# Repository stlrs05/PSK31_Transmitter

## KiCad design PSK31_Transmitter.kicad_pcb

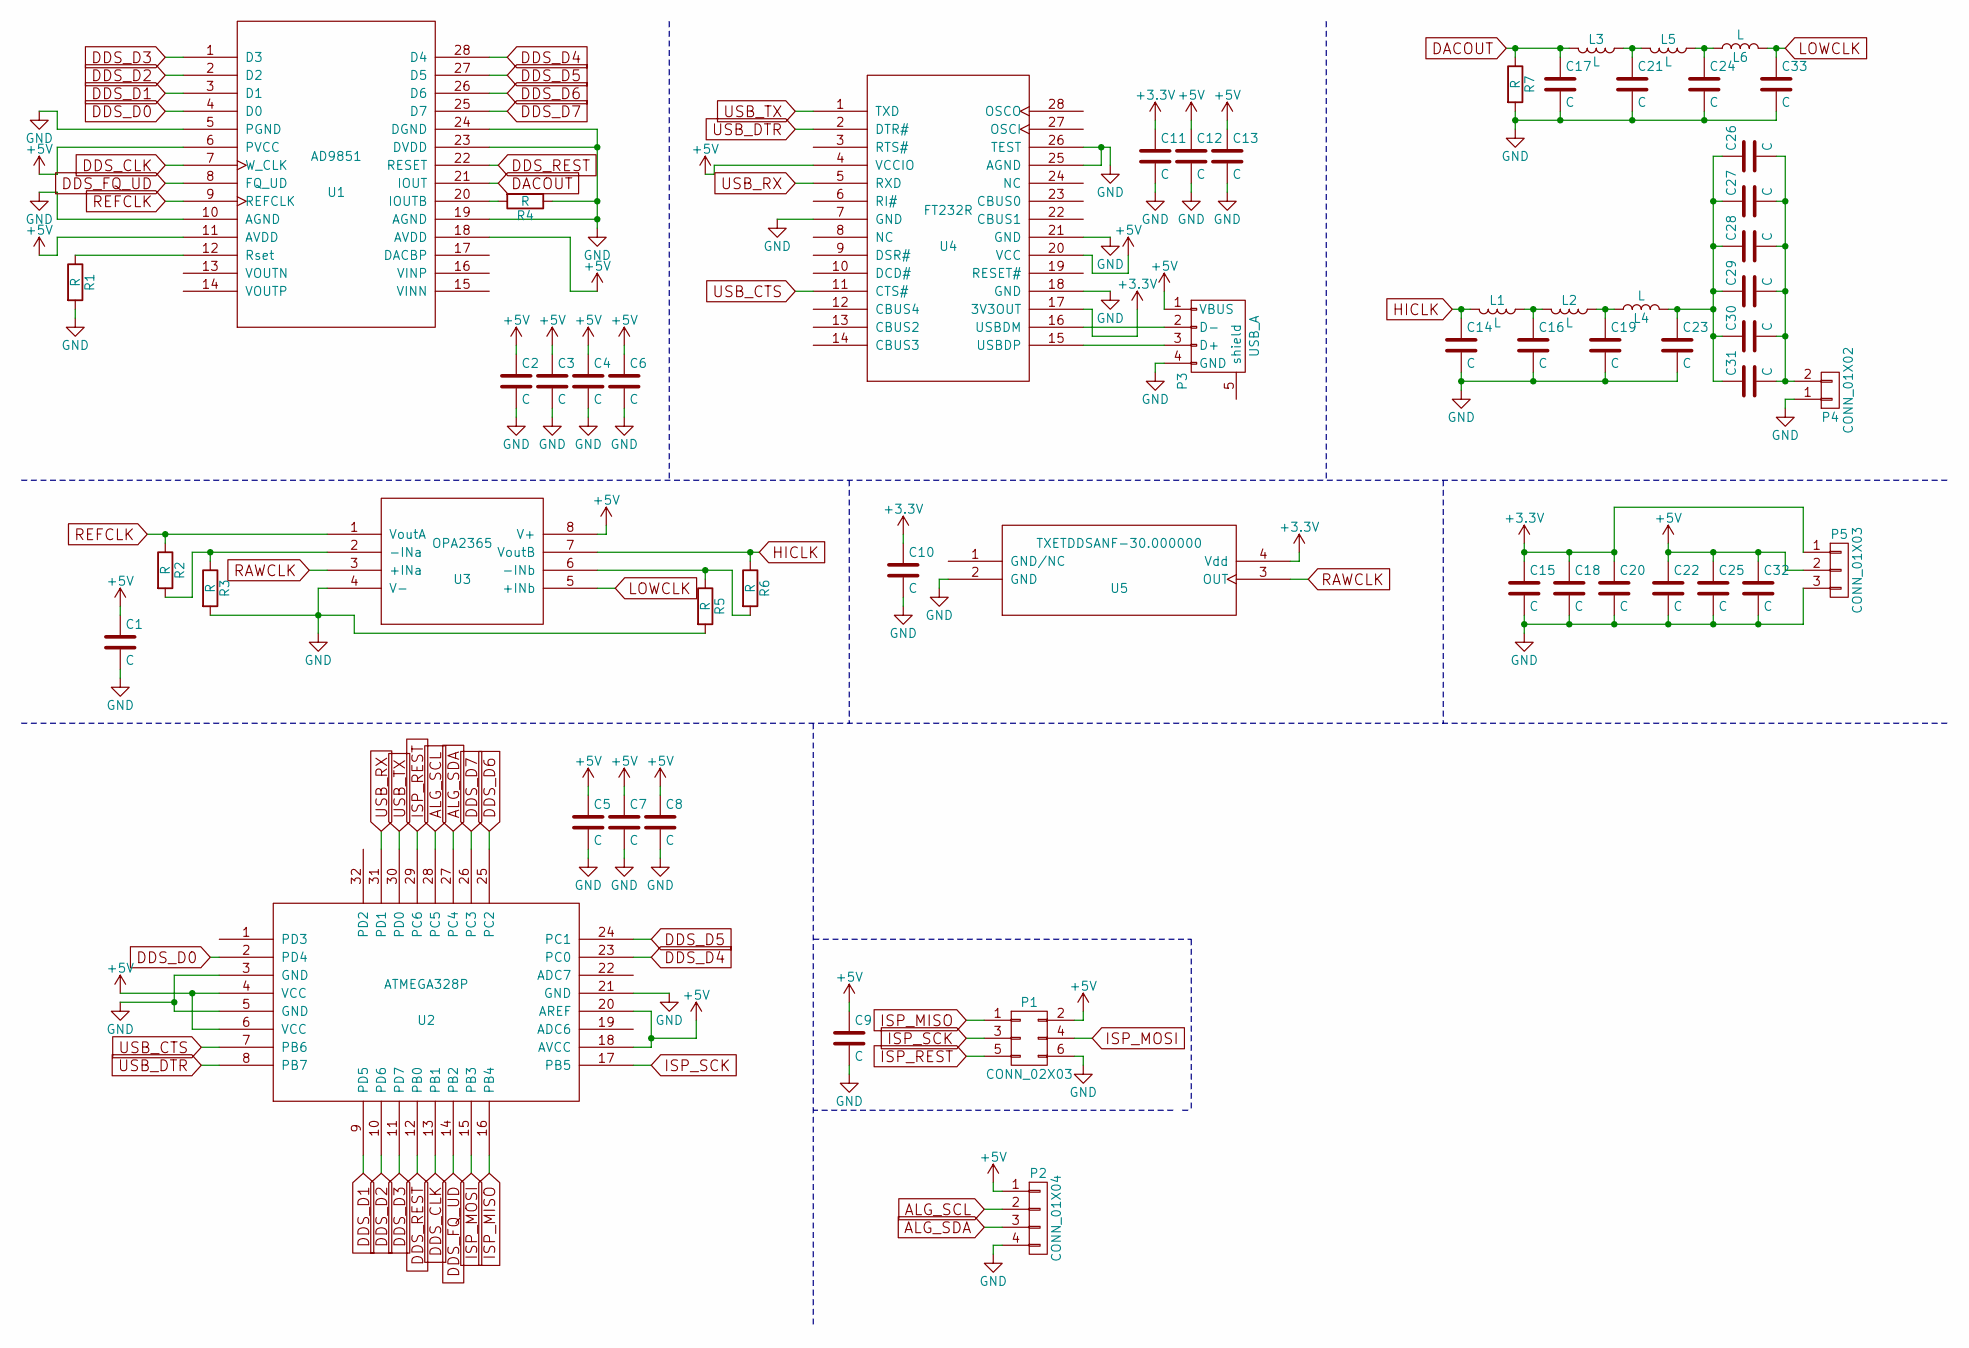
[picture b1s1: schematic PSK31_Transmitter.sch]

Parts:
C1, C2, C3, C4, C5, C6, C7, C8, C9, C10, C11, C12, C13, C14, C15, C16, C17, C18, C19, C20, C21, C22, C23, C24, C25, C26, C27, C28, C29, C30, C31, C32, C33: C; C_1206_HandSoldering
L1, L2, L3, L4, L5, L6: L; L_1206_Handsoldering
P1: CONN_02X03; Pin_Header_Angled_2x03_Pitch2.54mm
P2: CONN_01X04; Pin_Header_Angled_1x04_Pitch2.54mm
P3: USB_A
P4: CONN_01X02; UMC
P5: CONN_01X03; Pin_Header_Angled_1x03_Pitch2.54mm
R1, R2, R3, R4, R5, R6, R7: R; R_1206_HandSoldering
U1: AD9851; SSOP-28_5.3x10.2mm_Pitch0.65mm
U2: ATMEGA328P; TQFP-32_7x7mm_Pitch0.8mm
U3: OPA2365; SOIC-8_3.9x4.9mm_Pitch1.27mm
U4: FT232R; SSOP-28_5.3x10.2mm_Pitch0.65mm
U5: TXETDDSANF-30.000000; Oscillator_SMD_TXC_7C-4pin_5.0x3.2mm_HandSoldering

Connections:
+3V3: C10.1, C11.1, C15.1, C18.1, C20.1, P5.1, U4.17 (3V3OUT), U5.4 (Vdd)
+5V: C1.1, C2.1, C3.1, C4.1, C5.1, C6.1, C7.1, C8.1, C9.1, C12.1, C13.1, C22.1, C25.1, C32.1, P1.2, P2.1, P3.1 (VBUS), P5.2, U1.6 (PVCC), U1.11 (AVDD), U1.18 (AVDD), U2.4 (VCC), U2.6 (VCC), U2.18 (AVCC), U2.20 (AREF), U3.8 (V+), U4.4 (VCCIO), U4.20 (VCC)
ALG_SCL: P2.2, U2.28 (PC5)
ALG_SDA: P2.3, U2.27 (PC4)
DACOUT: C17.1, L3.2, R7.1, U1.21 (IOUT)
DDS_CLK: U1.7 (W_CLK), U2.13 (PB1)
DDS_D0: U1.4 (D0), U2.2 (PD4)
DDS_D1: U1.3 (D1), U2.9 (PD5)
DDS_D2: U1.2 (D2), U2.10 (PD6)
DDS_D3: U1.1 (D3), U2.11 (PD7)
DDS_D4: U1.28 (D4), U2.23 (PC0)
DDS_D5: U1.27 (D5), U2.24 (PC1)
DDS_D6: U1.26 (D6), U2.25 (PC2)
DDS_D7: U1.25 (D7), U2.26 (PC3)
DDS_FQ_UD: U1.8 (FQ_UD), U2.14 (PB2)
DDS_REST: U1.22 (RESET), U2.12 (PB0)
GND: C1.2, C2.2, C3.2, C4.2, C5.2, C6.2, C7.2, C8.2, C9.2, C10.2, C11.2, C12.2, C13.2, C14.2, C15.2, C16.2, C17.2, C18.2, C19.2, C20.2, C21.2, C22.2, C23.2, C24.2, C25.2, C32.2, C33.2, P1.6, P2.4, P3.4 (GND), P4.1, P5.3, R1.2, R3.2, R4.1, R5.2, R7.2, U1.5 (PGND), U1.10 (AGND), U1.19 (AGND), U1.23 (DVDD), U1.24 (DGND), U2.3 (GND), U2.5 (GND), U2.21 (GND), U3.4 (V-), U4.7 (GND), U4.18 (GND), U4.21 (GND), U4.25 (AGND), U4.26 (TEST), U5.2 (GND)
HICLK: C14.1, L1.2, R6.1, U3.7 (VoutB)
ISP_MISO: P1.1, U2.16 (PB4)
ISP_MOSI: P1.4, U2.15 (PB3)
ISP_REST: P1.5, U2.29 (PC6)
ISP_SCK: P1.3, U2.17 (PB5)
LOWCLK: C33.1, L6.2, U3.5 (+INb)
unnamed: C16.1, L1.1, L2.2
unnamed: C19.1, L2.1, L4.1
unnamed: C21.1, L3.1, L5.2
unnamed: C23.1, C26.1, C27.1, C28.1, C29.1, C30.1, C31.1, L4.2
unnamed: C24.1, L5.1, L6.1
unnamed: C26.2, C27.2, C28.2, C29.2, C30.2, C31.2, P4.2
unnamed: P3.2 (D-), U4.16 (USBDM)
unnamed: P3.3 (D+), U4.15 (USBDP)
unnamed: R1.1, U1.12 (Rset)
unnamed: R2.2, R3.1, U3.2 (-INa)
unnamed: R4.2, U1.20 (IOUTB)
unnamed: R5.1, R6.2, U3.6 (-INb)
RAWCLK: U3.3 (+INa), U5.3 (OUT)
REFCLK: R2.1, U1.9 (REFCLK), U3.1 (VoutA)
USB_CTS: U2.7 (PB6), U4.11 (CTS#)
USB_DTR: U2.8 (PB7), U4.2 (DTR#)
USB_RX: U2.31 (PD1), U4.5 (RXD)
USB_TX: U2.30 (PD0), U4.1 (TXD)

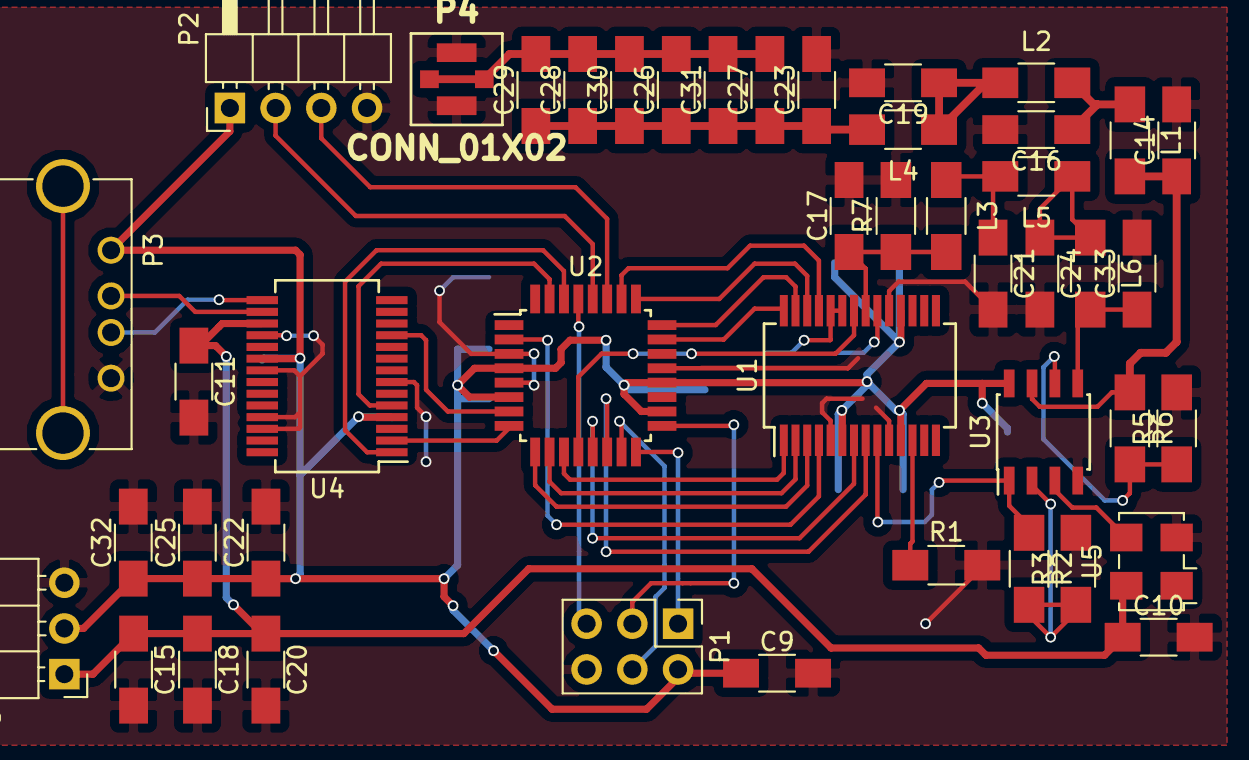
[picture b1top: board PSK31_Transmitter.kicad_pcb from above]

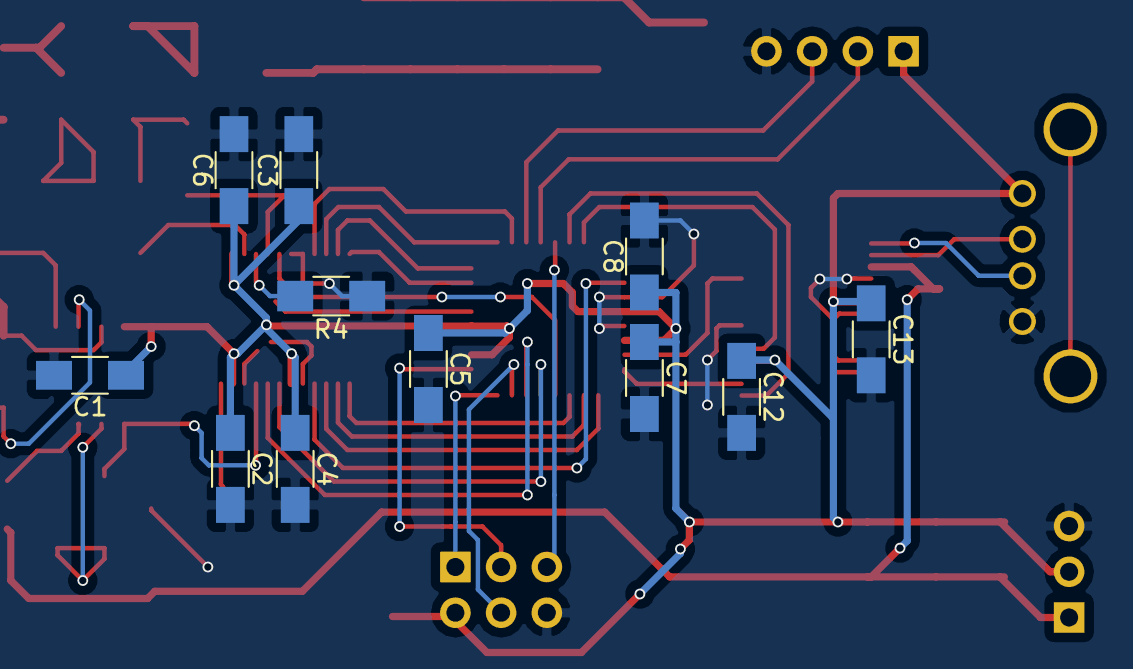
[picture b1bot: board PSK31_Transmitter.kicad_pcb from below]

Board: 2 copper layers, 56 parts (11 on the bottom side), 41 nets.

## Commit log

2017-06-15 Add shift registers and counters
2017-06-15 Add microcontroller and pll
2017-06-15 Remove counters and shift registers
2017-06-15 Replaced pll with dds
2017-06-16 Replace dds with pll and prepare for new microcontroller
2017-06-16 Replace mcu and add ftdi chip
2017-06-20 Replace pll with dds
2017-06-21 Add filters and amplifer
2017-06-21 Add ftdi support circuitry and connect dds to mcu
2017-06-22 Add external circuitry for ftdi and dds.
2017-06-28 Add dac filter and dds reference clock
2017-06-29 Add dds clock amplifer/filter and add dds output amplifier/filter
